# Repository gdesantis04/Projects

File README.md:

# Fall 2025 Engineering Projects

This repository contains selected engineering projects from Fall 2025, organized into separate project folders.

## Projects

### 1. Lowpass Filter Design
Design of a 50-ohm microstrip low-pass filter on FR-4 with a 3 GHz cutoff frequency, Chebyshev response, and attenuation verification.

### 2. CMS ETL Test Stand Design Review
Capstone design review for an automated test stand supporting verification of RB3, RB6, and RB7 readout boards for the CMS Endcap Timing Layer upgrade.

### 3. ASIC Emulator Final Project
ELEC 434 final project involving an ASIC emulator for voltage monitoring, 500 kHz clock generation, and synchronous power-good output.

## Repository structure

```text
Fall-2025-Projects-GitHub-Ready/
├── Lowpass-Filter-Design/
├── CMS-ETL-Test-Stand-Design-Review/
└── ASIC-Emulator-Final-Project/
```

Each folder includes its own README and the relevant project files.

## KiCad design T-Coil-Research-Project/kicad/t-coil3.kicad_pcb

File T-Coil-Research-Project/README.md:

# PCB-Embedded T-Coil for Expanding Channel Bandwidth

This repository contains the design files and documentation for a PCB-embedded bridged T-coil project. The goal of the project was to compensate for heavy load capacitance, such as capacitance introduced by ESD protection, and improve high-frequency channel bandwidth using PCB-embedded inductors. 

## Project Summary

The project investigates a bridged T-coil implemented with PCB transmission-line structures. The design was supported by simulation and layout work, then validated through fabricated-board measurements. The final result showed that the fabricated T-coils reduced loss on channels with parasitic capacitance. We tried to implement the same technique that Nvidia is using on SERDES chips on transmission lines in the Gigahertz range. Our advisor for this project was Dr. Thanh Tran at Rice University. 

## Repository Structure

```text
T-Coil-Research-Project/
├── README.md
├── .gitignore
├── docs/
│   ├── T-Coil-Paper.pdf
│   └── T-Coil-Design-Presentation.pdf
├── kicad/
│   ├── t-coil3.kicad_pro
│   ├── t-coil3.kicad_sch
│   ├── t-coil3.kicad_pcb
│   ├── t-coil3.kicad_prl
│   └── t-coil3.hyp
└── fabrication/
    ├── t-coil3-odb.zip
    └── gerbers/
```

## Contents

- `docs/` contains the final paper and project presentation.
- `kicad/` contains the KiCad schematic, PCB layout, project file, and HyperLynx file.
- `fabrication/` contains manufacturing outputs, including Gerbers, drill files, and an ODB++ archive.

## Tools Used

- KiCad for schematic capture and PCB layout
- Ansys HFSS and Siemens HyperLynx for simulation and electromagnetic design support
- Vector network analyzer measurements for experimental validation

## Endorsement by Dr. Tran
https://www.linkedin.com/feed/update/urn:li:activity:7458952096684404736/

## Authors

Mitchell Hoffman, Zheng Wei Low, and Guido De Santis  
Department of Electrical and Computer Engineering, Rice University

## Notes

This repository has been cleaned for GitHub. Temporary files, macOS metadata, KiCad lock files, local cache files, and automatic backup archives were removed.

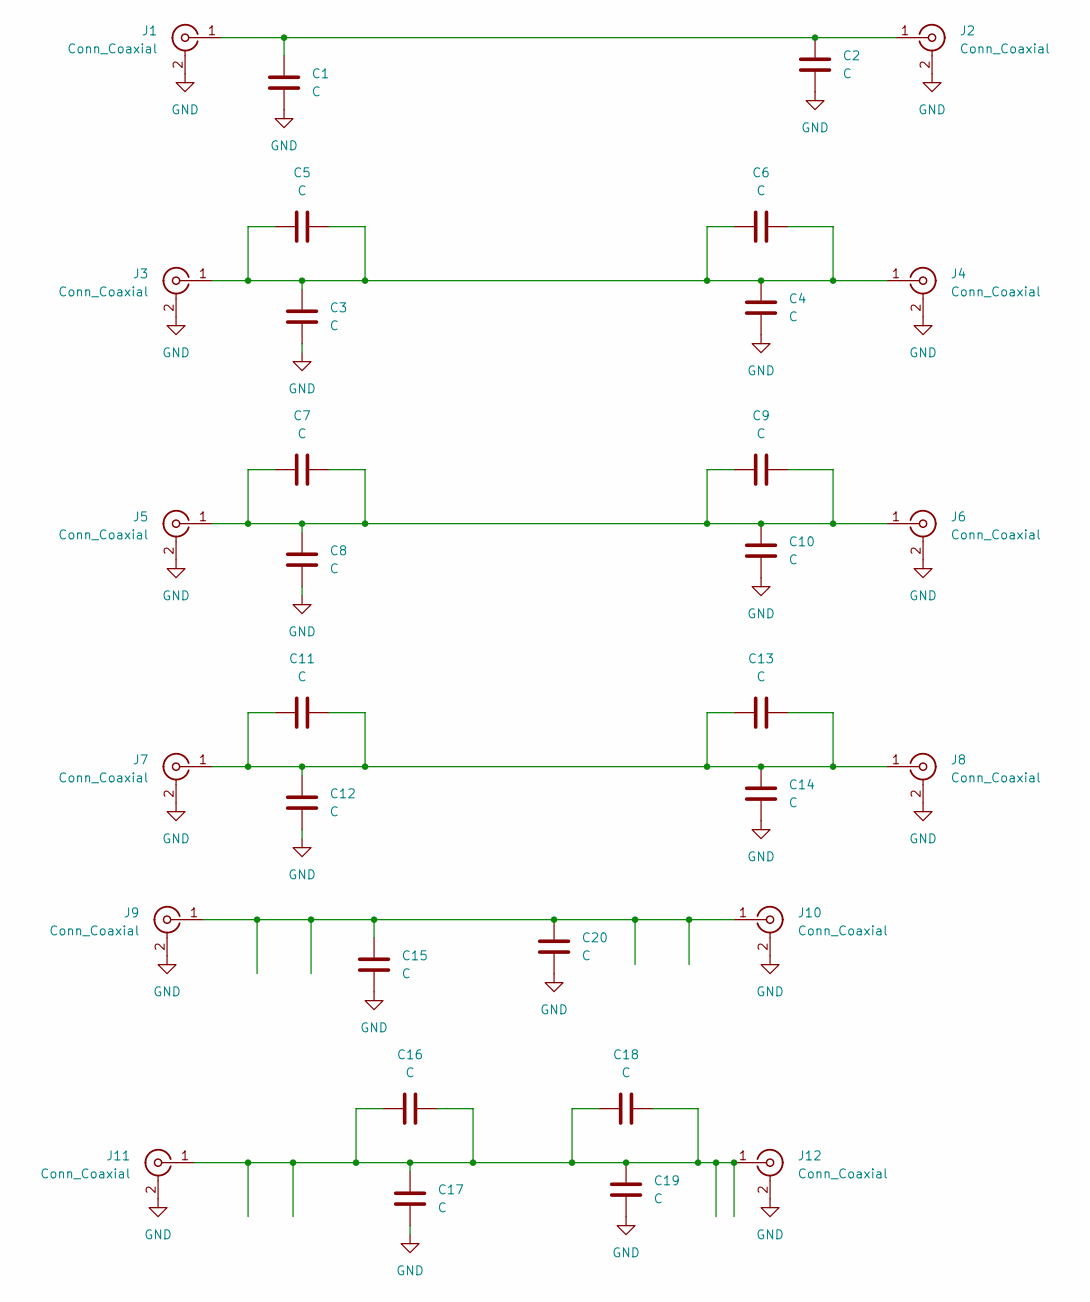
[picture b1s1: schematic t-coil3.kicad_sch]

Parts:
C1, C2, C3, C4, C5, C6, C7, C8, C9, C10, C11, C12, C13, C14, C15, C16, C17, C18, C19, C20: C; C_0603_1608Metric_Pad1.08x0.95mm_HandSolder
J1, J2, J3, J4, J5, J6, J7, J8, J9, J10, J11, J12: Conn_Coaxial; SMA_Molex_73251-1153_EdgeMount_Horizontal

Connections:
GND: C1.2, C2.2, C3.2, C4.2, C8.2, C10.2, C12.2, C14.2, C15.2, C17.2, C19.2, C20.2, J1.2 (Ext), J2.2 (Ext), J3.2 (Ext), J4.2 (Ext), J5.2 (Ext), J6.2 (Ext), J7.2 (Ext), J8.2 (Ext), J9.2 (Ext), J10.2 (Ext), J11.2 (Ext), J12.2 (Ext)
unnamed: C1.1, C2.1, J1.1 (In), J2.1 (In)
unnamed: C3.1, C4.1, C5.1, C5.2, C6.1, C6.2, J3.1 (In), J4.1 (In)
unnamed: C7.1, C7.2, C8.1, C9.1, C9.2, C10.1, J5.1 (In), J6.1 (In)
unnamed: C11.1, C11.2, C12.1, C13.1, C13.2, C14.1, J7.1 (In), J8.1 (In)
unnamed: C15.1, C20.1, J9.1 (In), J10.1 (In)
unnamed: C16.1, C16.2, C17.1, C18.1, C18.2, C19.1, J11.1 (In), J12.1 (In)

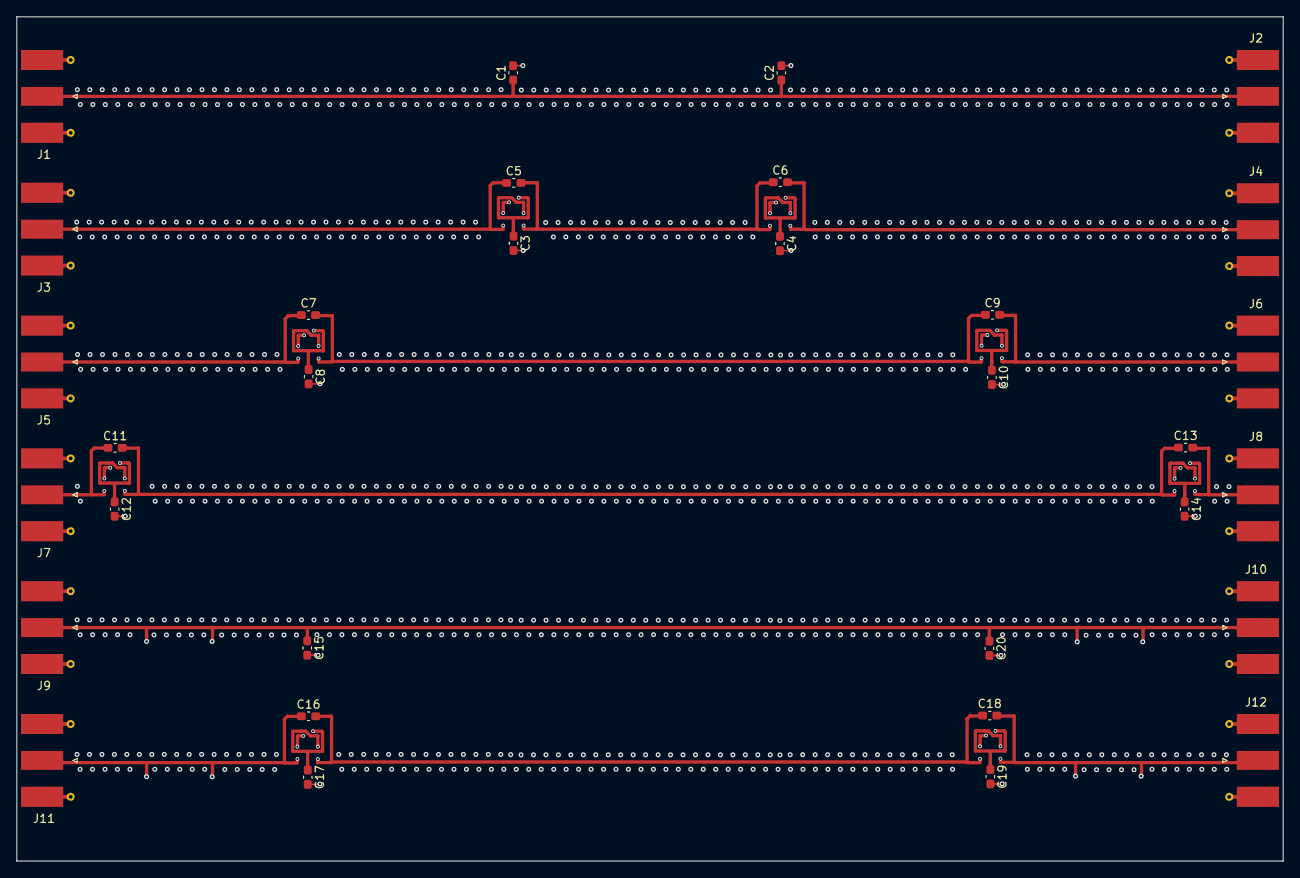
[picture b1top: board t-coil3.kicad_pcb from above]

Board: 4 copper layers, 152.4 x 101.6 mm, 32 parts (0 on the bottom side), 7 nets.

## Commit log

2026-06-23 Add files via upload
    t coil
2026-06-23 Add files via upload
    projects from fall 2025
2026-06-23 Add files via upload
    t coil research project
